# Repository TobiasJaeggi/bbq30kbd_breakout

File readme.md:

# Blackberry Q30 (Passport) Keyboard breakout board
Based on [bbq10kbd_breakout](https://github.com/arturo182/bbq10kbd_breakout), Q30 pinout reverse engineered by [TinLethax](https://hackaday.io/project/184529-reverse-engineering-bb-passport-keyboard/log/209494-k0uchpad-ble).

Blackberry Q30 keyboard connector breakout board using Hirose BM14B(0.8)-24DS-0.4V(53).

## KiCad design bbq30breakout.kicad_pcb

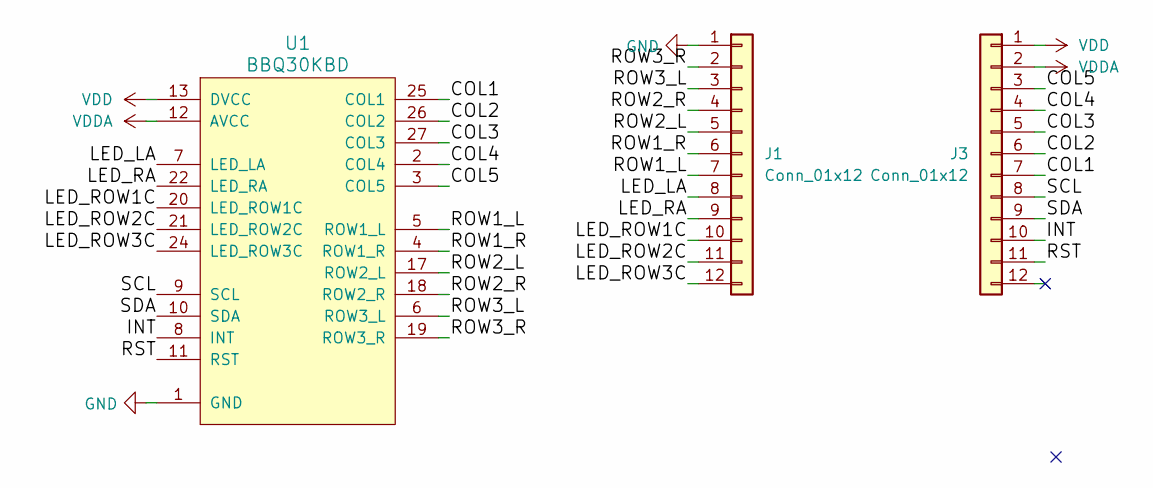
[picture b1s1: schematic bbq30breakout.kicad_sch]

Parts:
J1, J3: Conn_01x12; PinHeader_1x12_P2.54mm_Vertical
U1: BBQ30KBD; BM14B(0.8)-24DS-0.4V(53)

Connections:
/COL1: J3.7, U1.25 (COL1)
/COL2: J3.6, U1.26 (COL2)
/COL3: J3.5, U1.27 (COL3)
/COL4: J3.4, U1.2 (COL4)
/COL5: J3.3, U1.3 (COL5)
/INT: J3.10, U1.8 (INT)
/LED_LA: J1.8, U1.7 (LED_LA)
/LED_RA: J1.9, U1.22 (LED_RA)
/LED_ROW1C: J1.10, U1.20 (LED_ROW1C)
/LED_ROW2C: J1.11, U1.21 (LED_ROW2C)
/LED_ROW3C: J1.12, U1.24 (LED_ROW3C)
/ROW1_L: J1.7, U1.5 (ROW1_L)
/ROW1_R: J1.6, U1.4 (ROW1_R)
/ROW2_L: J1.5, U1.17 (ROW2_L)
/ROW2_R: J1.4, U1.18 (ROW2_R)
/ROW3_L: J1.3, U1.6 (ROW3_L)
/ROW3_R: J1.2, U1.19 (ROW3_R)
/RST: J3.11, U1.11 (RST)
/SCL: J3.8, U1.9 (SCL)
/SDA: J3.9, U1.10 (SDA)
GND: J1.1, U1.1 (GND), U1.14 (GND), U1.15 (GND), U1.16 (GND), U1.23 (GND), U1.28 (GND)
VDD: J3.1, U1.13 (DVCC)
VDDA: J3.2, U1.12 (AVCC)

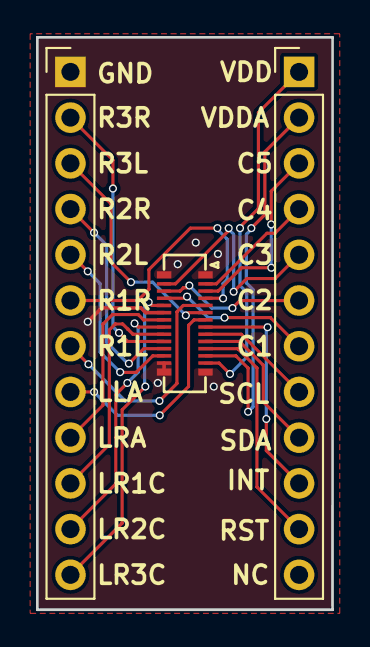
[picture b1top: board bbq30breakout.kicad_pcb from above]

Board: 2 copper layers, 16.4 x 31.8 mm, 3 parts (0 on the bottom side), 23 nets.
